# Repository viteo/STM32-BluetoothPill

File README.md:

# STM32-BluetoothPill
STM32 BluePill but with bluetooth KiCAD PCB Design

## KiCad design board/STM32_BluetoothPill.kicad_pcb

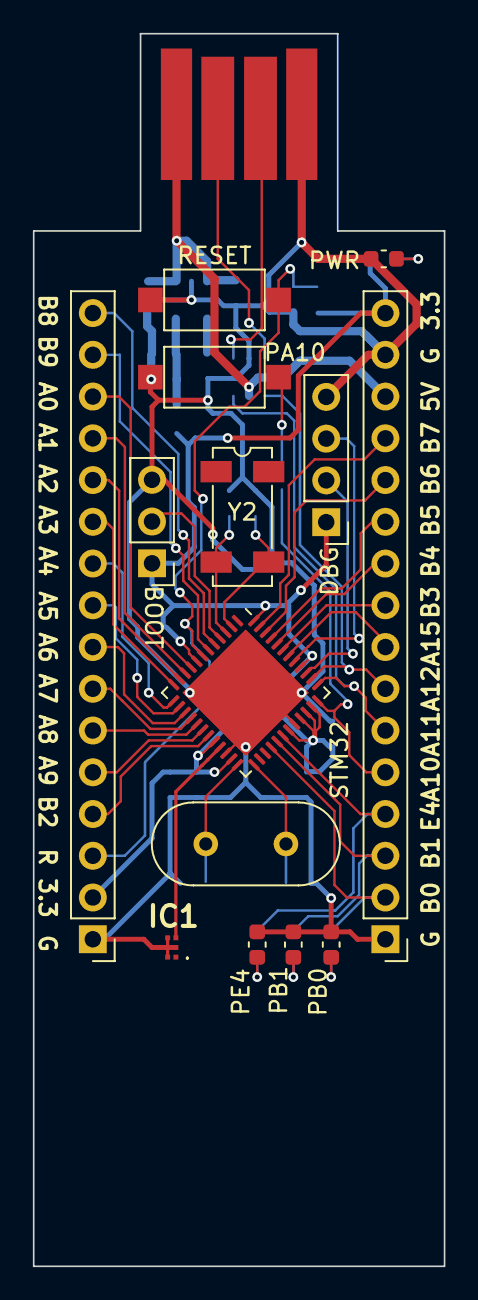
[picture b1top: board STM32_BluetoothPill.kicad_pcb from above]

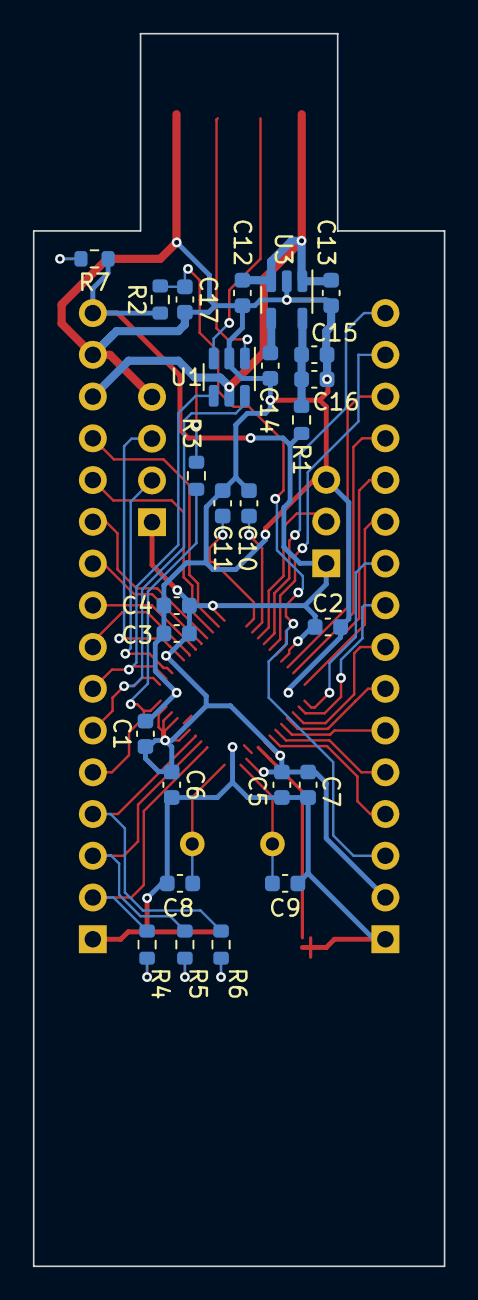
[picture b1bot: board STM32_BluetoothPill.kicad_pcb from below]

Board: 2 copper layers, 25.0 x 75.0 mm, 41 parts (26 on the bottom side), 46 nets.

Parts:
BOOT: Jumper_3_Open; PinHeader_1x03_P2.54mm_Vertical
C1, C2, C3, C4, C5, C6, C7, C8, C9, C10, C11, C12, C13, C14, C15, C16, C17: C_Small; C_0603_1608Metric
DBG: Conn_01x04; PinHeader_1x04_P2.54mm_Vertical
IC1: MLPF-WB-01E3; MLPFWB01E3
J1: USB_A; CONN-USB-A-PCB-TRACES
J3, J4: Conn_01x16; PinHeader_1x16_P2.54mm_Vertical
PA10: SW_Push; SW_SPST_CK_RS282G05A3
PB0, PB1: LED_Small; C_0603_1608Metric
PE4: LED_Small; C_0603_1608Metric
PWR: LED_Small; C_0603_1608Metric
R1, R2, R3, R4, R5, R6, R7: R_Small; R_0603_1608Metric
RESET: SW_Push; SW_SPST_CK_RS282G05A3
STM32: STM32WB55CEU6TR; QFN-48-1EP_7x7mm_P0.5mm_EP5.45x5.45mm
U1: USBLC6-2SC6; SOT-23-6
U3: LD3985M33R_SOT23; SOT-23-5
Y1: Crystal_Small; Crystal_HC49-4H_Vertical
Y2: Crystal_Small; Crystal_SMD_SeikoEpson_MC306-4Pin_8.0x3.2mm

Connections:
+3.3V: BOOT.1 (A), C1.1, C2.1, C3.1, C4.1, C5.1, C6.1, C7.1, DBG.1, J3.2, J4.16, R1.1, R2.1, R7.1, STM32.8 (VDDA), STM32.20 (VDD), STM32.23 (VDDRF), STM32.31 (VFBSMPS), STM32.33 (VLXSMPS), STM32.34 (VDDSMPS), STM32.35 (VDD), STM32.40 (VDDUSB), STM32.48 (VDD)
+5V: C12.1, C13.1, J1.1 (VBUS), J4.14, U1.5 (VBUS), U3.1 (VIN), U3.3 (INH)
/D+: J1.2 (D-), U1.3 (I/O2)
/D-: J1.3 (D+), U1.1 (I/O1)
GND: BOOT.3 (B), C1.2, C2.2, C3.2, C4.2, C5.2, C6.2, C7.2, C8.2, C9.2, C10.2, C11.2, C12.2, C13.2, C14.2, C15.2, C16.2, C17.2, DBG.4, IC1.A2 (GND4), IC1.B1 (GND3), IC1.B2 (GND2), IC1.B3 (GND1), J1.4 (GND), J3.1, J4.1, J4.15, PA10.1, PB0.1 (K), PB1.1 (K), PE4.1 (K), PWR.1 (K), RESET.1, STM32.22 (VSSRF), STM32.32 (VSSSMPS), STM32.49 (EXP), U1.2 (GND), U3.2 (GND)
unnamed: C8.1, STM32.25 (OSC_IN), Y1.1
unnamed: C9.1, STM32.24 (OSC_OUT), Y1.2
unnamed: C10.1, STM32.3 (PC15-OSC32_OUT), Y2.1
unnamed: C11.1, STM32.2 (PC14-OSC32_IN), Y2.2
unnamed: C14.1, U3.4 (BYP)
unnamed: C15.1, C16.1, R1.2, U3.5 (VOUT)
unnamed: PB0.2 (A), R4.2
unnamed: PB1.2 (A), R5.2
unnamed: PE4.2 (A), R6.2
unnamed: PWR.2 (A), R7.2
unnamed: IC1.A3 (IN), STM32.21 (RF1)
unnamed: BOOT.2 (C), STM32.4 (PH3-BOOT0)
unnamed: PA10.2, R3.2
PA0: J3.14, STM32.9 (PA0)
PA1: J3.13, STM32.10 (PA1)
PA2: J3.12, STM32.11 (PA2)
PA3: J3.11, STM32.12 (PA3)
PA4: J3.10, STM32.13 (PA4)
PA5: J3.9, STM32.14 (PA5)
PA6: J3.8, STM32.15 (PA6)
PA7: J3.7, STM32.16 (PA7)
PA8: J3.6, STM32.17 (PA8)
PA9: J3.5, STM32.18 (PA9)
PA10: J4.5, R3.1, STM32.36 (PA10)
PA15: J4.8, STM32.42 (PA15)
PB0: J4.2, R4.1, STM32.28 (PB0)
PB1: J4.3, R5.1, STM32.29 (PB1)
PB2: J3.4, STM32.19 (PB2)
PB3: J4.9, STM32.43 (PB3)
PB4: J4.10, STM32.44 (PB4)
PB5: J4.11, STM32.45 (PB5)
PB6: J4.12, STM32.46 (PB6)
PB7: J4.13, STM32.47 (PB7)
PB8: J3.16, STM32.5 (PB8)
PB9: J3.15, STM32.6 (PB9)
PE4: J4.4, R6.1, STM32.30 (PE4)
RESET: C17.1, J3.3, R2.2, RESET.2, STM32.7 (NRST)
SWCLK: DBG.3, STM32.41 (PA14)
SWDIO: DBG.2, STM32.39 (PA13)
USB_N: J4.6, STM32.37 (PA11), U1.6 (I/O1)
USB_P: J4.7, STM32.38 (PA12), U1.4 (I/O2)

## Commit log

2022-03-04 Power supply and GPIO
2022-03-04 RF shield
2022-03-04 gitignore for KiCad 6
2022-03-09 footprints designated
2022-03-10 pcb parts placement
2022-03-10 footprints changed gpio names added
2022-12-15 move to kicad 6 footprint updates
2022-12-15 DFM rules
2022-12-15 matched low pass filter added
2022-12-16 pcb first try
2022-12-20 folder organization
